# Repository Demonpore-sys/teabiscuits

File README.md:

# teabiscuits

All boards are currently initial revision, have not been brought-up/tested. LMP7721 designs have undergone some breadboarding.

teabiscuits_adc: MAX11169 Based ADC board, single ADC. Based on array board bringup, should work.

teabiscuits_adc_array: MAX11169 Based ADC board, array of 8 ADCs. Quick hack based on teabiscuits_adc. Works, requires hacks on power lines (overlaps with fill).

teabiscuits_adc_4ch: ADAR7521 Based 4 channel ADC board. Regulator comes up with reset, SPI not yet tested.

teabiscuits_amp: LMP7721 Based transimpedance amplifier, uses guarding circuit. Bring up started, see notes on notion.

teabiscuits_amp_mini: LMP7721 Based amplifier, attempt to make a very small board, no guarding. Tested, works.

teabiscuits_amp_mini_bias: LMP7721 Based board with bias control, has been built. r3 will require modifications (see notion)

teabiscuits_dac: AD5791 Based DAC/Bias board.

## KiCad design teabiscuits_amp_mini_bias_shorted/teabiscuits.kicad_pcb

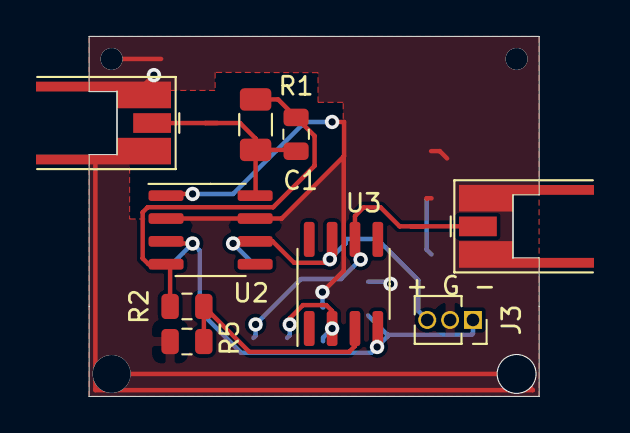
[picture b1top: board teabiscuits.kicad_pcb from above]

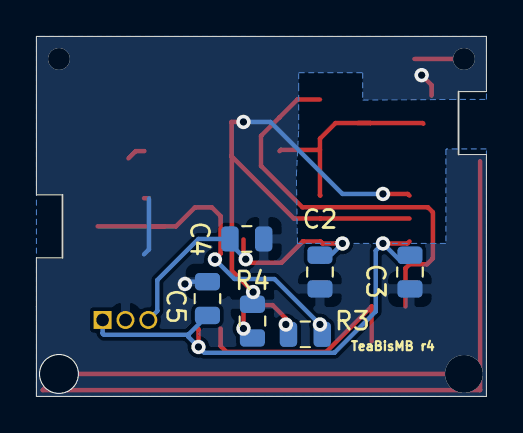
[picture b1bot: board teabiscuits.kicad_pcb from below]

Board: 2 copper layers, 24.9 x 20.0 mm, 15 parts (6 on the bottom side), 8 nets.

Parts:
C1: 2pF; C_0805_2012Metric
C2, C3: 100nF; C_0805_2012Metric
C4, C5: 10nF; C_0805_2012Metric
J1, J2: Conn_Coaxial; MMCX_Molex_73415-0961_Horizontal_1.0mm-PCB
J3: Conn_01x03_Male; PinSocket_1x03_P1.27mm_Vertical
R1: 1M; R_1206_3216Metric
R2, R4: 100; R_0805_2012Metric
R3, R5: 1K; R_0805_2012Metric
U2: LMP7721; SOIC-8_3.9x4.9mm_P1.27mm
U3: OP07; SOIC-8_3.9x4.9mm_P1.27mm

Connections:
+5V: C2.1, C4.1, J3.3, U2.6, U3.7
-5V: C3.1, C5.1, J3.1, U2.3, U3.4
GUARD: C2.2, C3.2, C4.2, C5.2, J1.2, J2.2, J3.2, R4.1, R5.2, U2.1, U2.2, U2.7
unnamed: C1.1, R1.1, R2.2, U2.4
unnamed: C1.2, J1.1, R1.2, U2.8
unnamed: J2.1, R3.1, U3.6
unnamed: R2.1, R5.1, U3.3
unnamed: R3.2, R4.2, U3.2

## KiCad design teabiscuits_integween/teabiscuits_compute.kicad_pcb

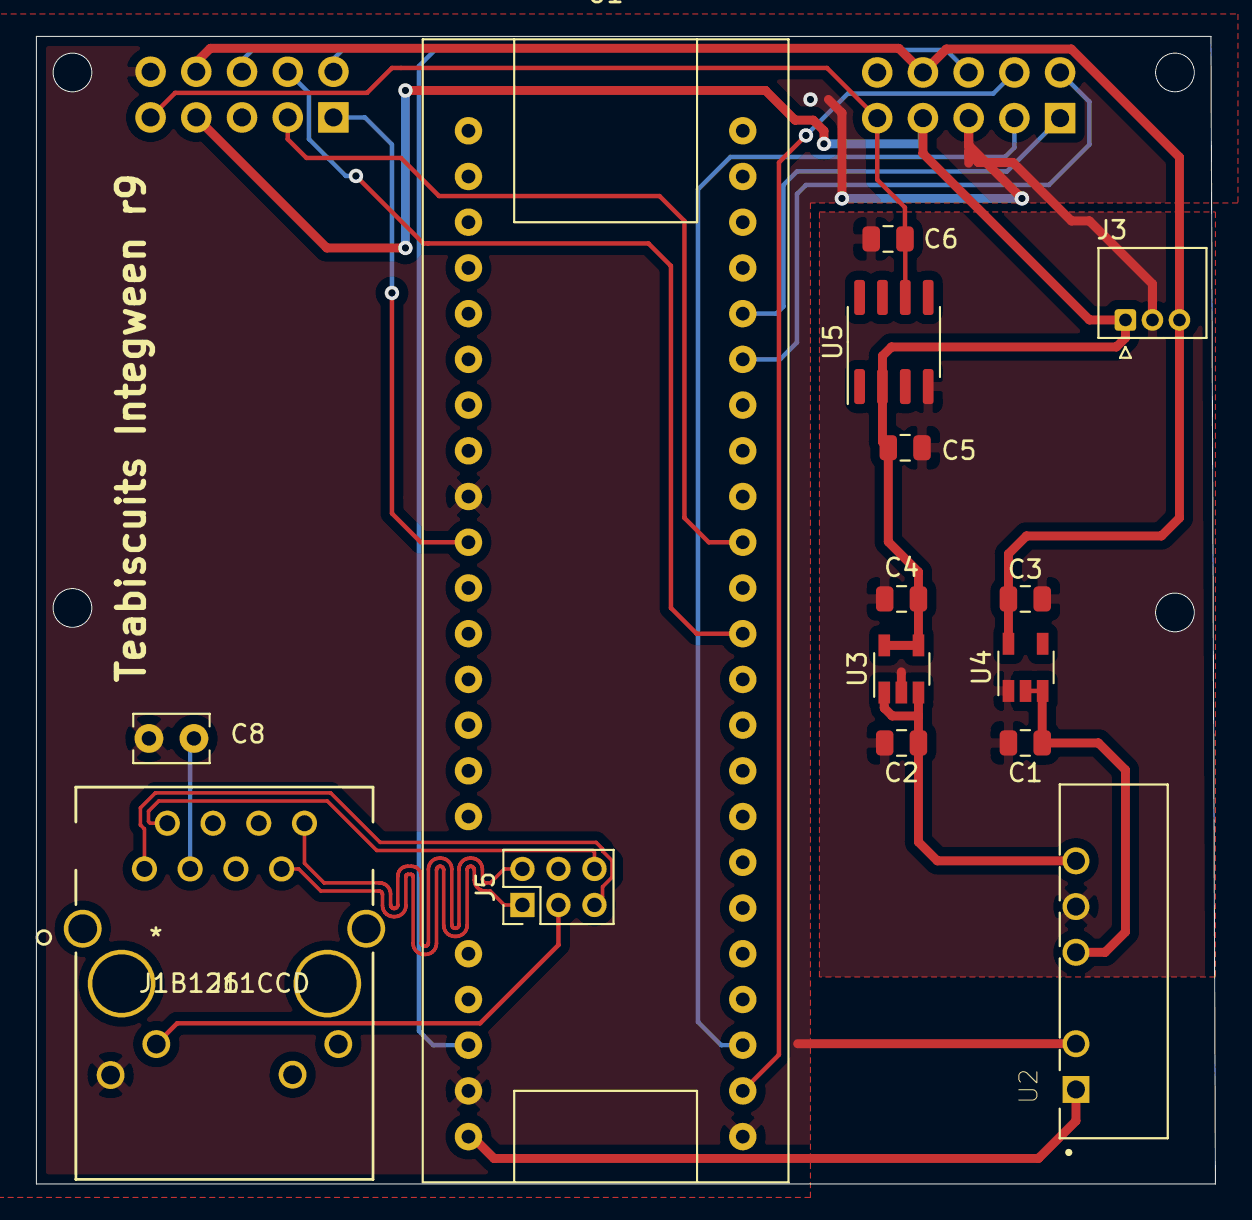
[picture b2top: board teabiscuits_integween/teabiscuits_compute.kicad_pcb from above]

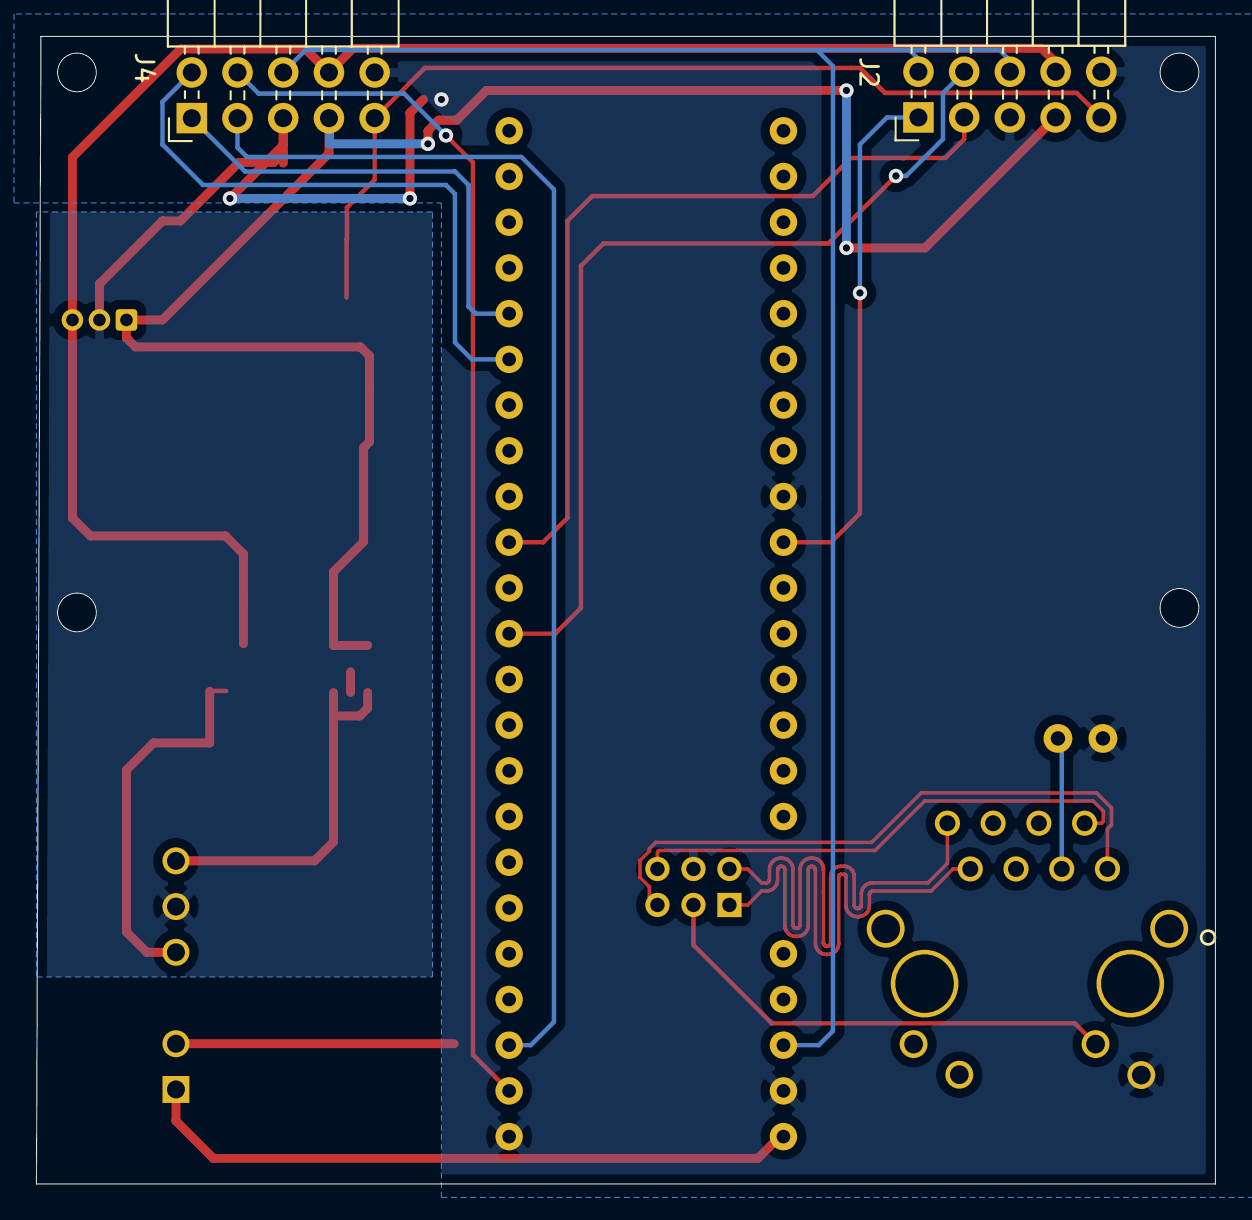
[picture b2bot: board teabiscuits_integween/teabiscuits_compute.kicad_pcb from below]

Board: 2 copper layers, 65.5 x 63.8 mm, 17 parts (2 on the bottom side), 21 nets.

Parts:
C1, C2, C3, C4: 2.2uF; C_0805_2012Metric
C5, C6: 0.1uF; C_0805_2012Metric
C8: CP; C_Rect_L4.0mm_W2.5mm_P2.50mm
J2, J4: Conn_02x05_Odd_Even; PinHeader_2x05_P2.54mm_Horizontal
J3: Conn_01x03; JST
J5: Conn_02x03_Odd_Even; PinHeader_2x03_P2.00mm_Vertical
J6: J1B1211CCD
U1: teensy41
U2: PDME1-S5-D3-S; CONV_PDME1-S5-D3-S
U3: ADP7142AUJZ-2.5; TSOT-23-5
U4: ADP7182AUJZ-2.5; TSOT-23-5
U5: REF5020AD; SOIC-8_3.9x4.9mm_P1.27mm

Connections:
+2V5: C4.1, C5.1, J2.7, J3.1, J4.7, U3.4, U3.5, U5.2
+5V: U1.M6, U2.1
-2V5: C3.1, J2.8, J3.3, J4.8, U4.5
DAC_LDAC: J4.4, U1.0
GND: C1.2, C2.2, C3.2, C4.2, C5.2, C6.2, C8.1, J2.5, J2.10, J3.2, J4.5, J4.10, J5.4, J6.9, U1.M1, U1.M3, U1.M5, U2.2, U2.5, U3.2, U4.1, U5.4
IOREF: J2.2, J2.6, J4.6, U1.M4
LED: J5.3, J6.10
unnamed: C1.1, U2.4, U4.2, U4.3
unnamed: C2.1, U2.6, U3.1, U3.3
unnamed: C8.2, J6.3
R+: J5.1, J6.7
R-: J5.2, J6.8
REF: C6.1, J2.9, J4.9, U5.6
SPI1_MISO: J4.3, U1.1
SPI1_MOSI: J4.2, U1.26
SPI1_SCLK: J4.1, U1.27
SPI4_CS0: J2.4, U1.10
SPI4_MISO: J2.3, U1.12
SPI4_SCLK: J2.1, U1.13
T+: J5.6, J6.2
T-: J5.5, J6.1

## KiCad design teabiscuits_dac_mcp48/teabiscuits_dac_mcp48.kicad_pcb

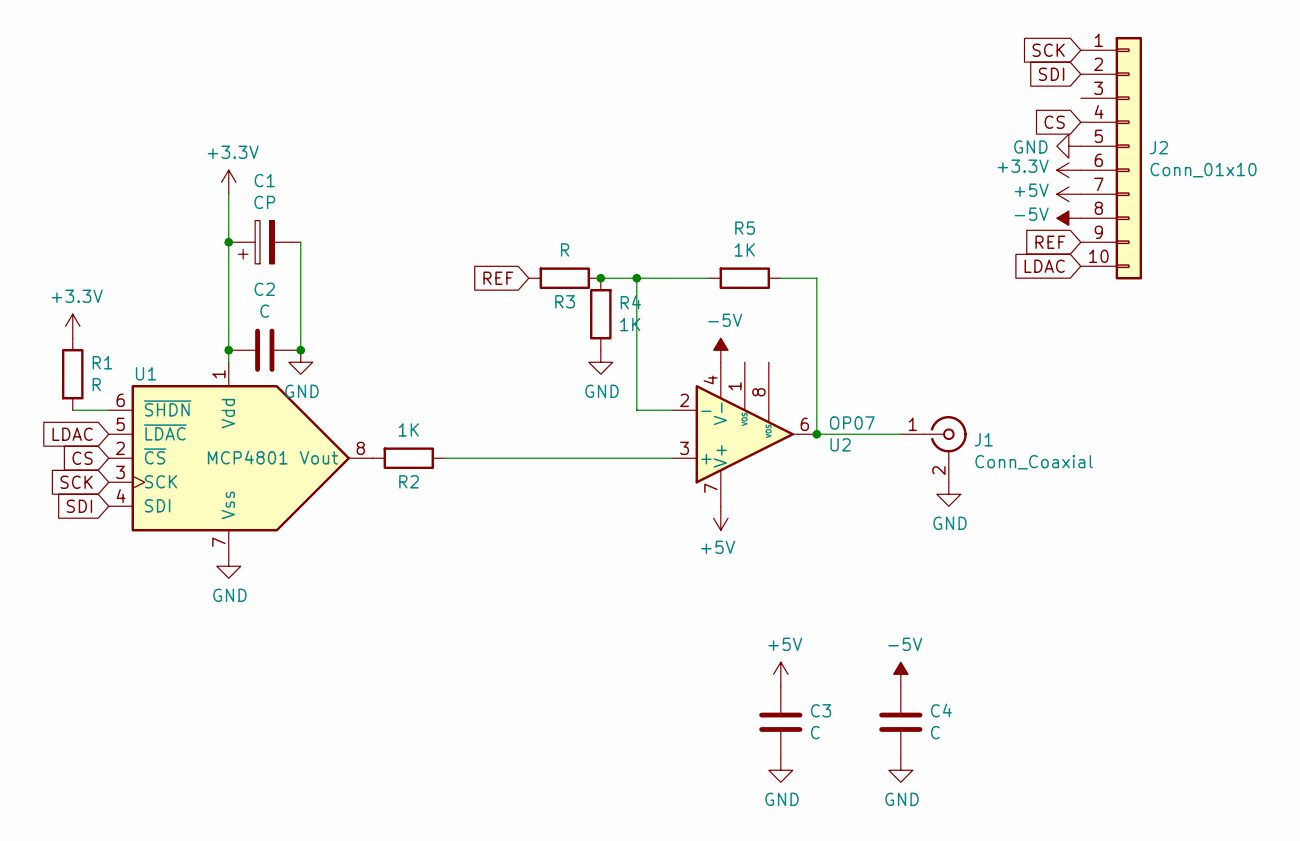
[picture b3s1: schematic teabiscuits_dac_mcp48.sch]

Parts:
C1: CP; CP_EIA-3216-18_Kemet-A
C2, C3, C4: C; C_1206_3216Metric
J1: Conn_Coaxial; MMCX_Molex_73415-0961_Horizontal_1.0mm-PCB
J2: Conn_01x10; PinHeader_2x05_P2.54mm_Horizontal
R1, R3: R; R_1206_3216Metric
R2, R4, R5: 1K; R_1206_3216Metric
U1: MCP4801; SOIC-8_3.9x4.9mm_P1.27mm
U2: OP07; SOIC-8_3.9x4.9mm_P1.27mm

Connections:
+3V3: C1.1, C2.2, J2.6, R1.1, U1.1 (Vdd)
+5V: C3.2, J2.7, U2.7 (V+)
-5V: C4.2, J2.8, U2.4 (V-)
CS: J2.4, U1.2 (~CS)
GND: C1.2, C2.1, C3.1, C4.1, J1.2 (Ext), J2.5, R4.1, U1.7 (Vss)
LDAC: J2.10, U1.5 (~LDAC)
unnamed: J1.1 (In), R5.1, U2.6
unnamed: R1.2, U1.6 (~SHDN)
unnamed: R2.1, U2.3 (+)
unnamed: R2.2, U1.8 (Vout)
unnamed: R3.1, R4.2, R5.2, U2.2 (-)
REF: J2.9, R3.2
SCK: J2.1, U1.3 (SCK)
SDI: J2.2, U1.4 (SDI)

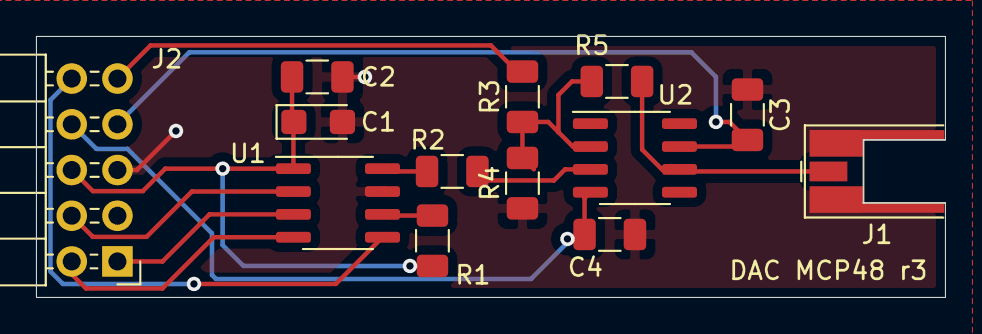
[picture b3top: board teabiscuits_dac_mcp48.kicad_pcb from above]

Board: 2 copper layers, 50.4 x 14.5 mm, 13 parts (0 on the bottom side), 14 nets.

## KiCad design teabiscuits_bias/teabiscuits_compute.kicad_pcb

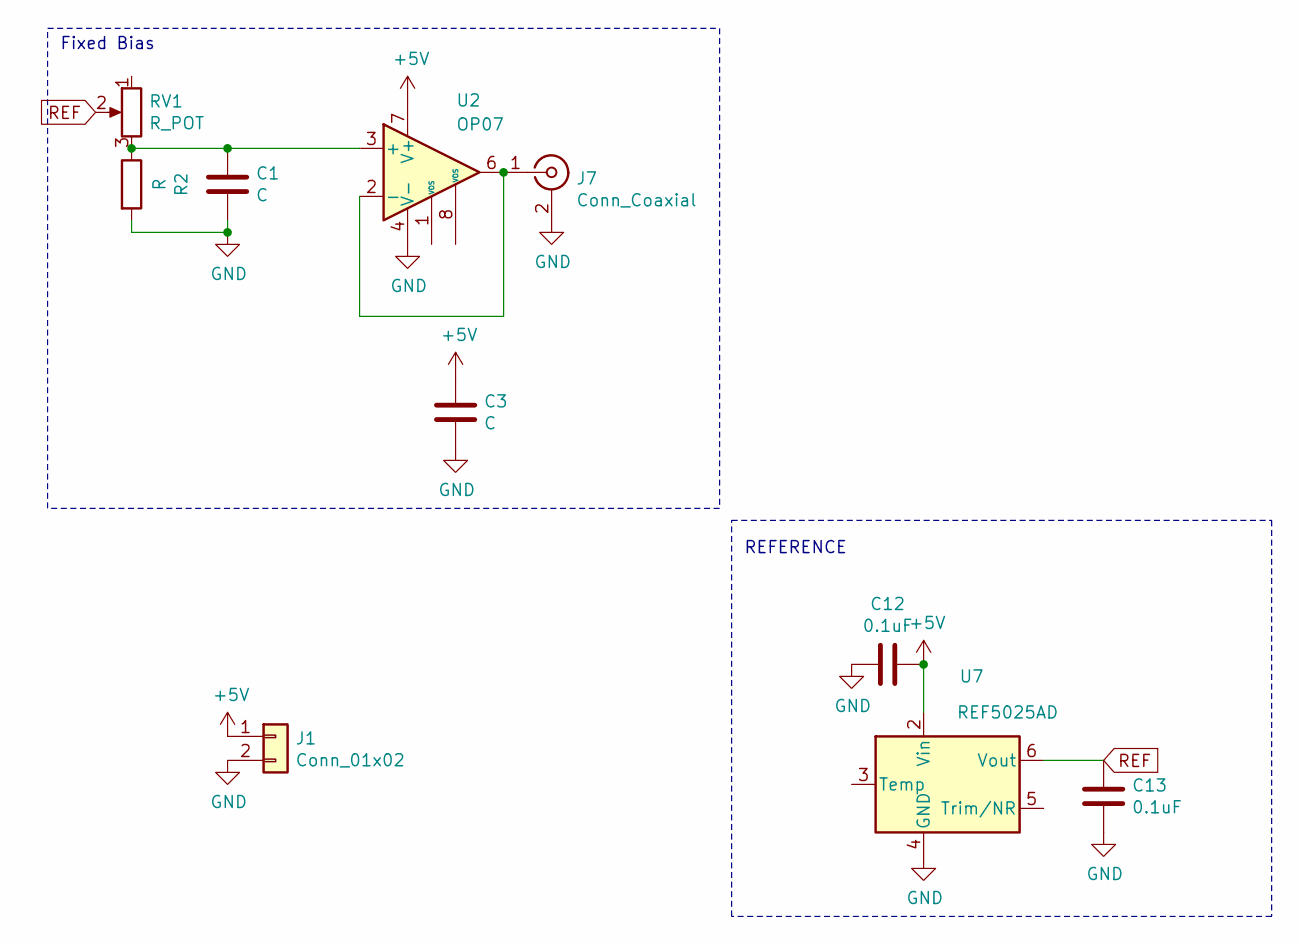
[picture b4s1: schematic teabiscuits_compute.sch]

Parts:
C1, C3: C; C_0805_2012Metric
C12, C13: 0.1uF; C_0805_2012Metric
J1: Conn_01x02; PinHeader_1x02_P2.54mm_Vertical
J7: Conn_Coaxial; MMCX_Molex_73415-0961_Horizontal_1.0mm-PCB
R2: R; R_0805_2012Metric
RV1: R_POT; Potentiometer_WirePads_largePads
U2: OP07; SOIC-8_3.9x4.9mm_P1.27mm
U7: REF5025AD; SOIC-8_3.9x4.9mm_P1.27mm

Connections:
+5V: C3.1, C12.1, J1.1, U2.7 (V+), U7.2 (Vin)
GND: C1.2, C3.2, C12.2, C13.2, J1.2, J7.2 (Ext), R2.2, U2.4 (V-), U7.4 (GND)
unnamed: C1.1, R2.1, RV1.3, U2.3 (+)
unnamed: J7.1 (In), U2.2 (-), U2.6
REF: C13.1, RV1.2, U7.6 (Vout)

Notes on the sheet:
Fixed Bias
REFERENCE

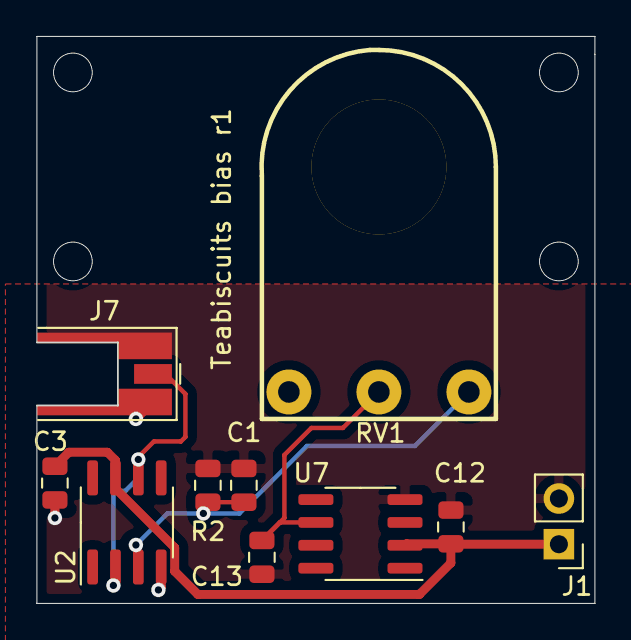
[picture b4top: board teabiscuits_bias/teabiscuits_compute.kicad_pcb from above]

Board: 2 copper layers, 31.0 x 31.4 mm, 10 parts (0 on the bottom side), 5 nets.

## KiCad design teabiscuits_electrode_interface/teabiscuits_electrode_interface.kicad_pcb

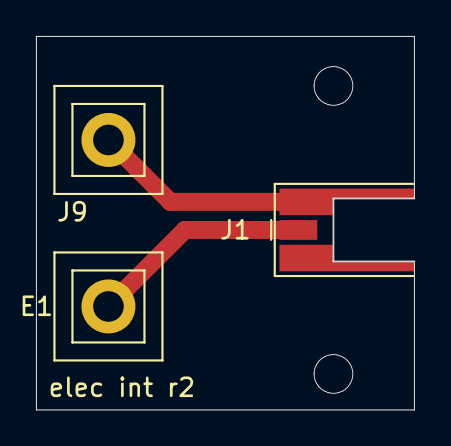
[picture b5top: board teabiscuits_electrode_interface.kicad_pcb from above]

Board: 2 copper layers, 21.0 x 20.7 mm, 3 parts (0 on the bottom side), 2 nets.

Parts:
E1: Conn_01x01; KeystonePost
J1: Conn_Coaxial; MMCX_Molex_73415-0961_Horizontal_1.0mm-PCB
J9: Conn_01x01; KeystonePost

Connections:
GND: J1.2, J9.1
unnamed: E1.1, J1.1

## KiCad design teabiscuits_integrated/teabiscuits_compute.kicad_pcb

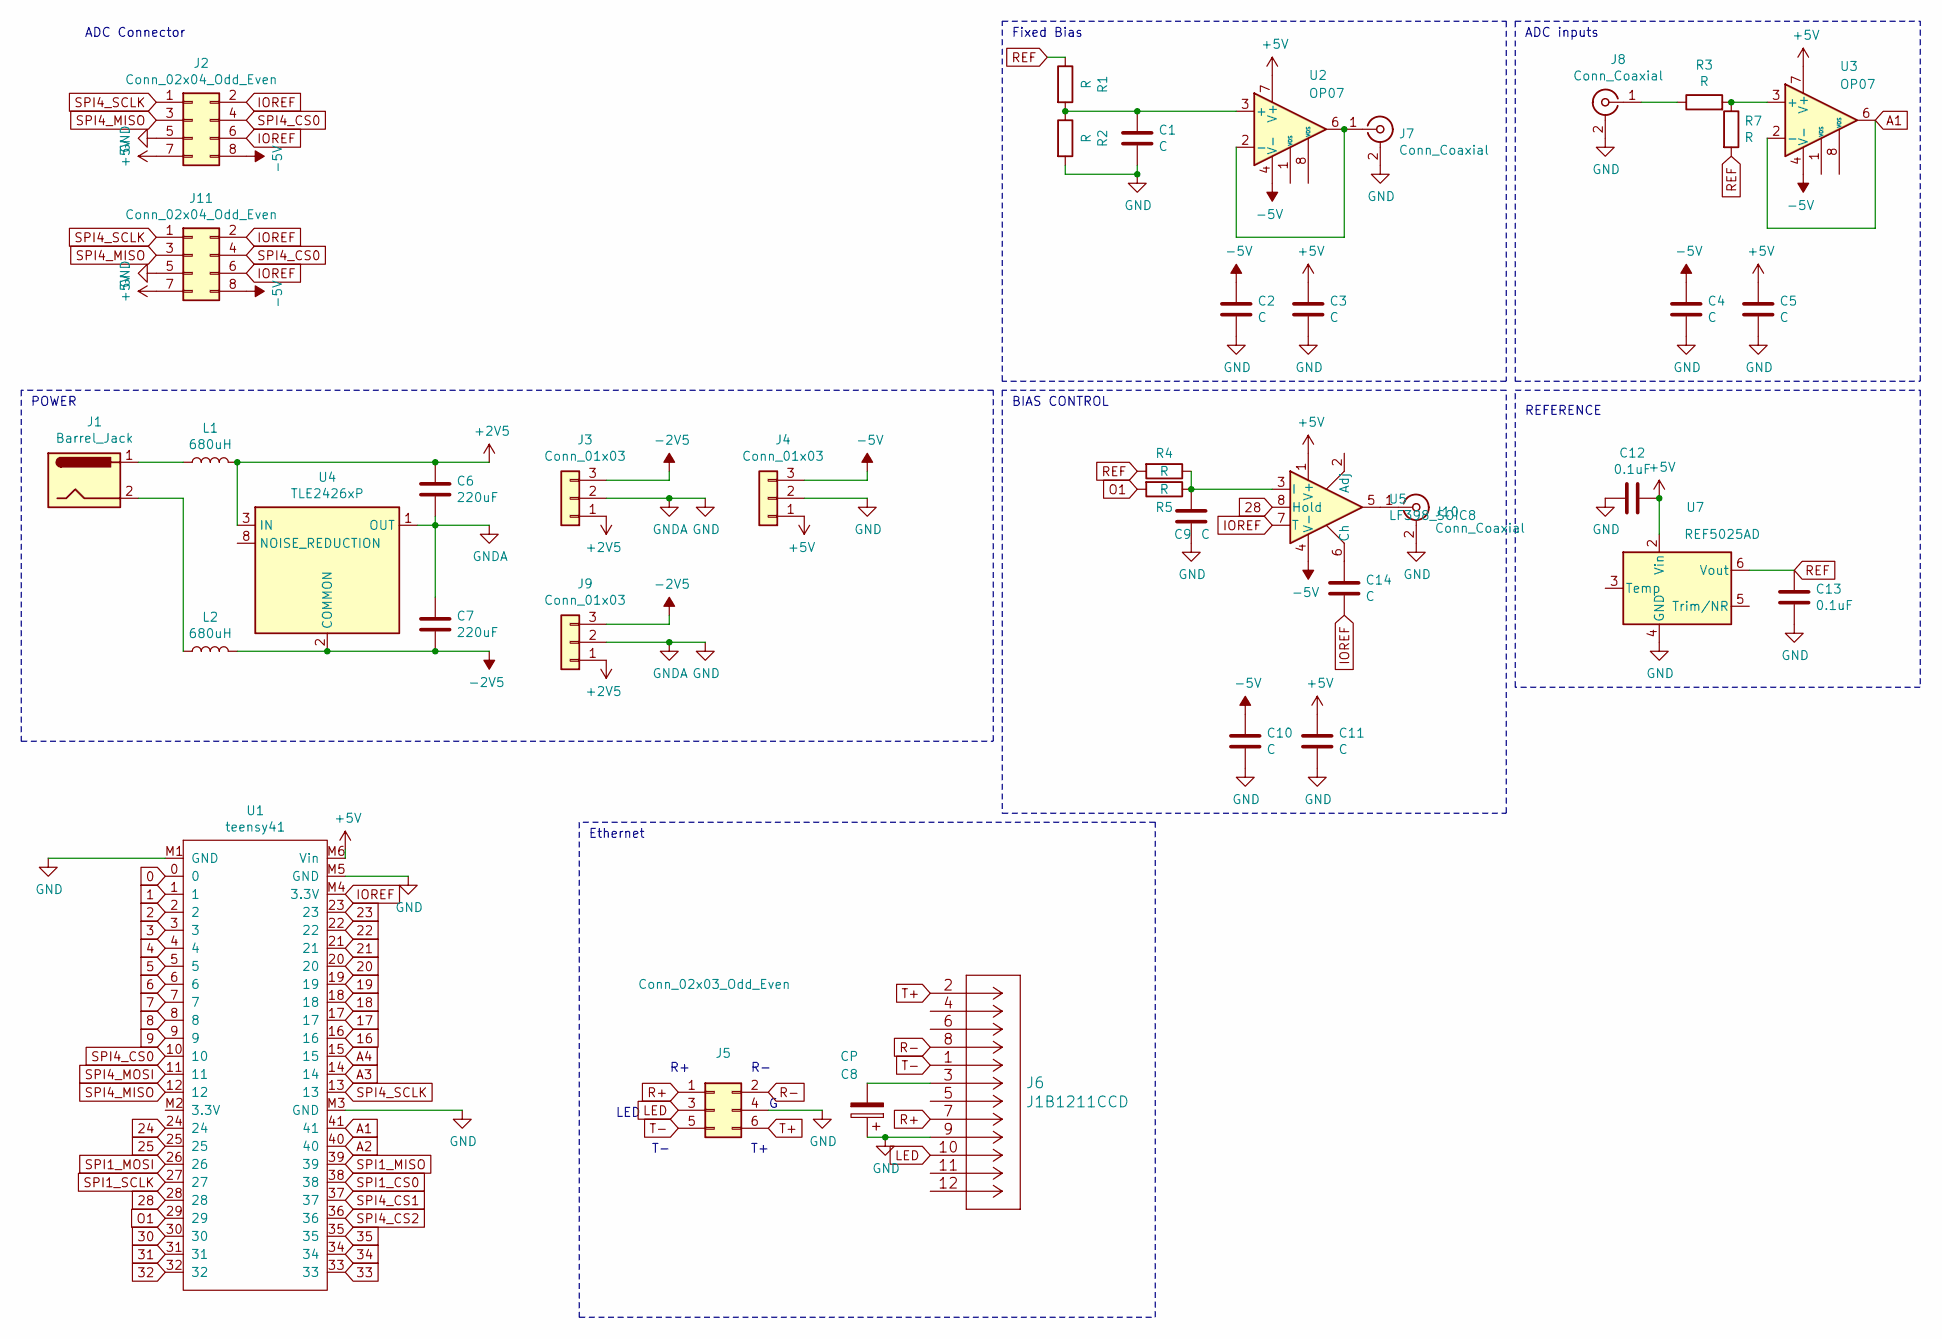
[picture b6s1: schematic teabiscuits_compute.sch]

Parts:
C1, C2, C3, C4, C5, C9, C10, C11, C14: C; C_0805_2012Metric
C6, C7: 220uF; CP_Radial_D5.0mm_P2.00mm
C8: CP; C_Rect_L4.0mm_W2.5mm_P2.50mm
C12, C13: 0.1uF; C_0805_2012Metric
J1: Barrel_Jack; BarrelJack_CUI_PJ-063AH_Horizontal
J2, J11: Conn_02x04_Odd_Even; PinHeader_2x04_P2.54mm_Vertical
J3, J4, J9: Conn_01x03; JST
J5: Conn_02x03_Odd_Even; PinHeader_2x03_P2.00mm_Vertical
J6: J1B1211CCD
J7, J8, J10: Conn_Coaxial; MMCX_Molex_73415-0961_Horizontal_1.0mm-PCB
L1, L2: 680uH; L_Radial_D9.5mm_P5.00mm_Fastron_07HVP
R1, R2, R3, R4, R5, R7: R; R_0805_2012Metric
U1: teensy41
U2, U3: OP07; SOIC-8_3.9x4.9mm_P1.27mm
U4: TLE2426xP; SOIC-8_3.9x4.9mm_P1.27mm
U5: LF398_SOIC8; SOIC-8_3.9x4.9mm_P1.27mm
U7: REF5025AD; SOIC-8_3.9x4.9mm_P1.27mm

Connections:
0: U1.0
1: U1.1
2: U1.2
3: U1.3
4: U1.4
5: U1.5
6: U1.6
7: U1.7
8: U1.8
9: U1.9
16: U1.16
17: U1.17
18: U1.18
19: U1.19
20: U1.20
21: U1.21
22: U1.22
23: U1.23
24: U1.24
25: U1.25
28: U1.28, U5.8 (Hold)
30: U1.30
31: U1.31
32: U1.32
33: U1.33
34: U1.34
35: U1.35
+2V5: C6.1, J3.1, J9.1, L1.2, U4.3 (IN)
+5V: C3.1, C5.1, C11.1, C12.1, J2.7, J4.1, J11.7, U1.M6 (Vin), U2.7 (V+), U3.7 (V+), U5.1 (V+), U7.2 (Vin)
-2V5: C7.2, J3.3, J9.3, L2.2, U4.2 (COMMON)
-5V: C2.1, C4.1, C10.1, J2.8, J4.3, J11.8, U2.4 (V-), U3.4 (V-), U5.4 (V-)
A1: U1.41, U3.2 (-), U3.6
A2: U1.40
A3: U1.14
A4: U1.15
GND: C1.2, C2.2, C3.2, C4.2, C5.2, C6.2, C7.1, C8.1, C9.2, C10.2, C11.2, C12.2, C13.2, J2.5, J3.2, J4.2, J5.4, J6.9, J7.2 (Ext), J8.2 (Ext), J9.2, J10.2 (Ext), J11.5, R2.2, U1.M1 (GND), U1.M3 (GND), U1.M5 (GND), U4.1 (OUT), U7.4 (GND)
IOREF: C14.2, J2.2, J2.6, J11.2, J11.6, U1.M4 (3.3V), U5.7 (T)
LED: J5.3, J6.10
unnamed: C1.1, R1.2, R2.1, U2.3 (+)
unnamed: C8.2, J6.3
unnamed: C9.1, R4.1, R5.1, U5.3 (I)
unnamed: C14.1, U5.6 (Ch)
unnamed: J1.1, L1.1
unnamed: J1.2, L2.1
unnamed: J7.1 (In), U2.2 (-), U2.6
unnamed: J8.1 (In), R3.1
unnamed: J10.1 (In), U5.5
unnamed: R3.2, R7.1, U3.3 (+)
O1: R5.2, U1.29
R+: J5.1, J6.7
R-: J5.2, J6.8
REF: C13.1, R1.1, R4.2, R7.2, U7.6 (Vout)
SPI1_CS0: U1.38
SPI1_MISO: U1.39
SPI1_MOSI: U1.26
SPI1_SCLK: U1.27
SPI4_CS0: J2.4, J11.4, U1.10
SPI4_CS1: U1.37
SPI4_CS2: U1.36
SPI4_MISO: J2.3, J11.3, U1.12
SPI4_MOSI: U1.11
SPI4_SCLK: J2.1, J11.1, U1.13
T+: J5.6, J6.2
T-: J5.5, J6.1

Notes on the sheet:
ADC inputs
Fixed Bias
ADC Connector
REFERENCE
BIAS CONTROL
POWER
Ethernet
LED

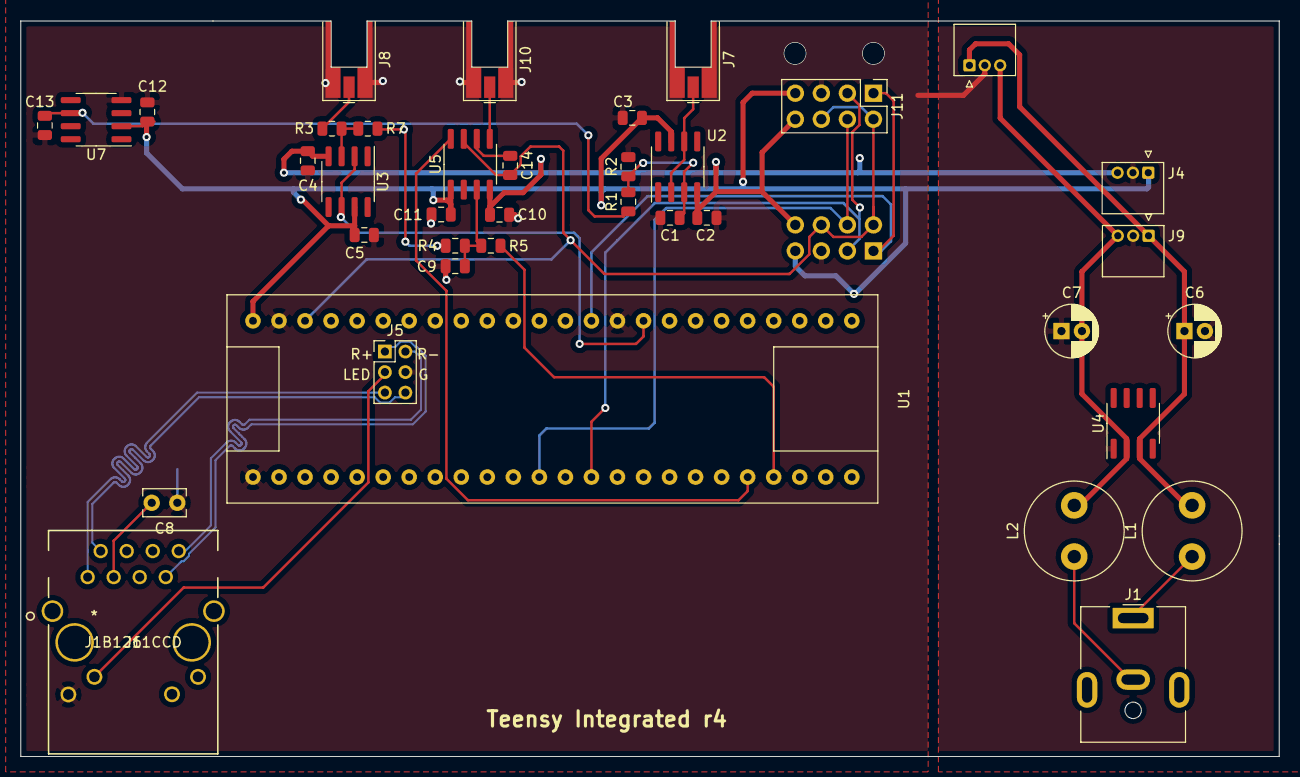
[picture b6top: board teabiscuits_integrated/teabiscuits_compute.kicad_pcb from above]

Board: 2 copper layers, 122.7 x 71.7 mm, 39 parts (1 on the bottom side), 28 nets.

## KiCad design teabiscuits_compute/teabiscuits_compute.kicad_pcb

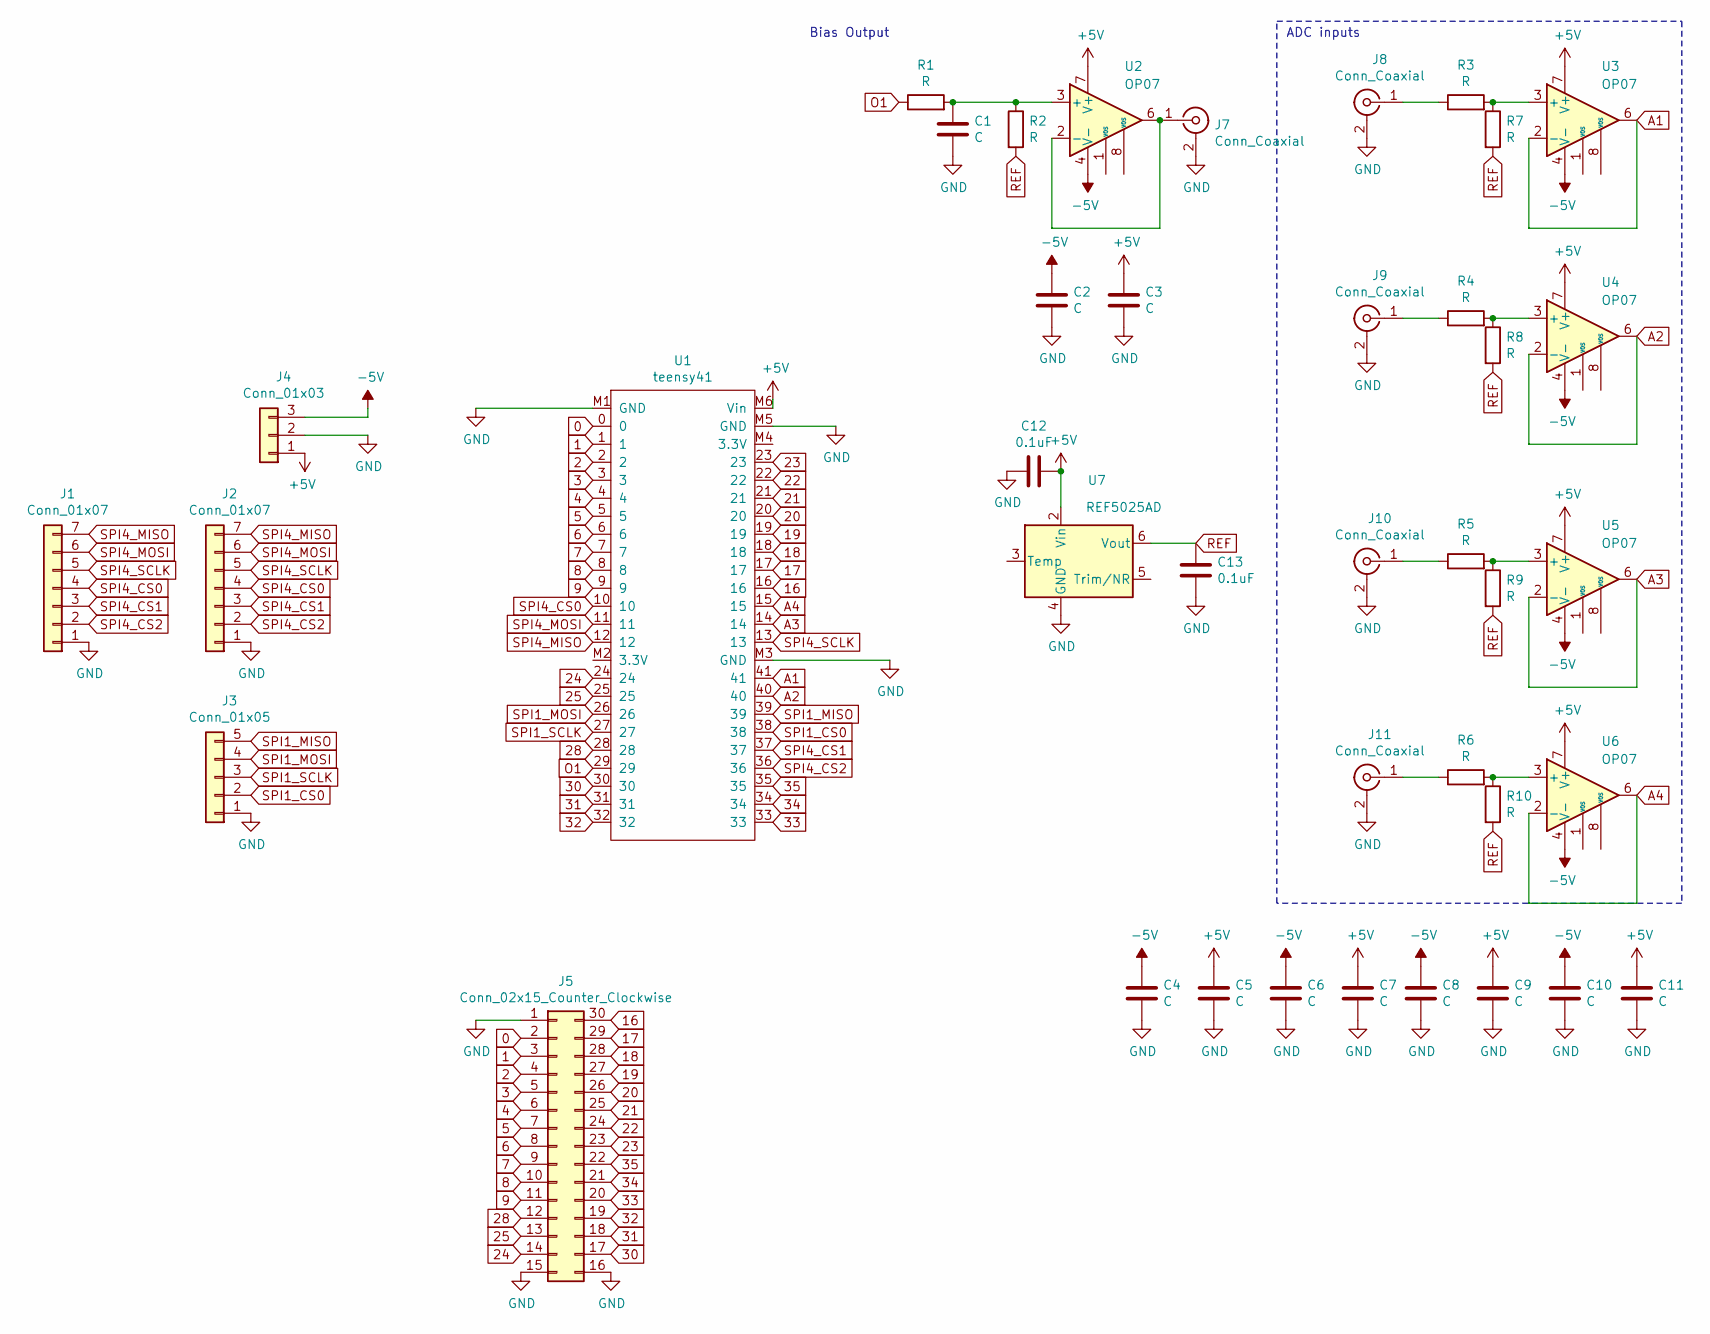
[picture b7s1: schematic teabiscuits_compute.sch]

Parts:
C1, C2, C3, C4, C5, C6, C7, C8, C9, C10, C11: C; C_0805_2012Metric
C12, C13: 0.1uF; C_0805_2012Metric
J1, J2: Conn_01x07; PinHeader_1x07_P2.54mm_Vertical
J3: Conn_01x05; PinHeader_1x05_P2.54mm_Vertical
J4: Conn_01x03; JST
J5: Conn_02x15_Counter_Clockwise; PinHeader_2x15_P2.54mm_Vertical
J7, J8, J9, J10, J11: Conn_Coaxial; MMCX_Molex_73415-0961_Horizontal_1.0mm-PCB
R1, R2, R3, R4, R5, R6, R7, R8, R9, R10: R; R_0805_2012Metric
U1: teensy41
U2, U3, U4, U5, U6: OP07; SOIC-8_3.9x4.9mm_P1.27mm
U7: REF5025AD; SOIC-8_3.9x4.9mm_P1.27mm

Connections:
0: J5.2, U1.0
1: J5.3, U1.1
2: J5.4, U1.2
3: J5.5, U1.3
4: J5.6, U1.4
5: J5.7, U1.5
6: J5.8, U1.6
7: J5.9, U1.7
8: J5.10, U1.8
9: J5.11, U1.9
16: J5.30, U1.16
17: J5.29, U1.17
18: J5.28, U1.18
19: J5.27, U1.19
20: J5.26, U1.20
21: J5.25, U1.21
22: J5.24, U1.22
23: J5.23, U1.23
24: J5.14, U1.24
25: J5.13, U1.25
28: J5.12, U1.28
30: J5.17, U1.30
31: J5.18, U1.31
32: J5.19, U1.32
33: J5.20, U1.33
34: J5.21, U1.34
35: J5.22, U1.35
A1: U1.41, U3.2 (-), U3.6
A2: U1.40, U4.2 (-), U4.6
A3: U1.14, U5.2 (-), U5.6
A4: U1.15, U6.2 (-), U6.6
GND: C1.2, C2.2, C3.2, C4.2, C5.2, C6.2, C7.2, C8.2, C9.2, C10.2, C11.2, C12.2, C13.2, J1.1, J2.1, J3.1, J4.2, J5.1, J5.15, J5.16, J7.2 (Ext), J8.2 (Ext), J9.2 (Ext), J10.2 (Ext), J11.2 (Ext), U1.M1 (GND), U1.M3 (GND), U1.M5 (GND), U7.4 (GND)
unnamed: C1.1, R1.2, R2.1, U2.3 (+)
unnamed: J7.1 (In), U2.2 (-), U2.6
unnamed: J8.1 (In), R3.1
unnamed: J9.1 (In), R4.1
unnamed: J10.1 (In), R5.1
unnamed: J11.1 (In), R6.1
unnamed: R3.2, R7.1, U3.3 (+)
unnamed: R4.2, R8.1, U4.3 (+)
unnamed: R5.2, R9.1, U5.3 (+)
unnamed: R6.2, R10.1, U6.3 (+)
O1: R1.1, U1.29
REF: C13.1, R2.2, R7.2, R8.2, R9.2, R10.2, U7.6 (Vout)
SPI1_CS0: J3.2, U1.38
SPI1_MISO: J3.5, U1.39
SPI1_MOSI: J3.4, U1.26
SPI1_SCLK: J3.3, U1.27
SPI4_CS0: J1.4, J2.4, U1.10
SPI4_CS1: J1.3, J2.3, U1.37
SPI4_CS2: J1.2, J2.2, U1.36
SPI4_MISO: J1.7, J2.7, U1.12
SPI4_MOSI: J1.6, J2.6, U1.11
SPI4_SCLK: J1.5, J2.5, U1.13

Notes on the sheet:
ADC inputs
Bias Output

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
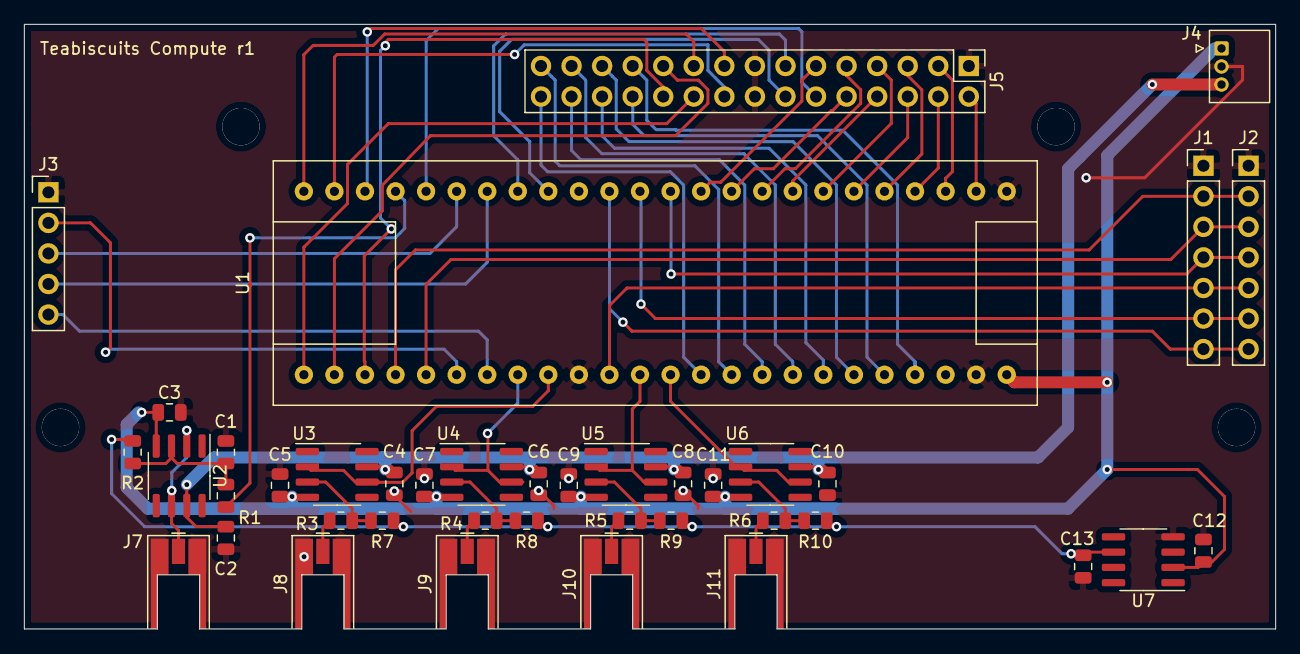
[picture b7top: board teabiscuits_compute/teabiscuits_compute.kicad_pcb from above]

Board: 2 copper layers, 104.0 x 50.2 mm, 40 parts (0 on the bottom side), 56 nets.

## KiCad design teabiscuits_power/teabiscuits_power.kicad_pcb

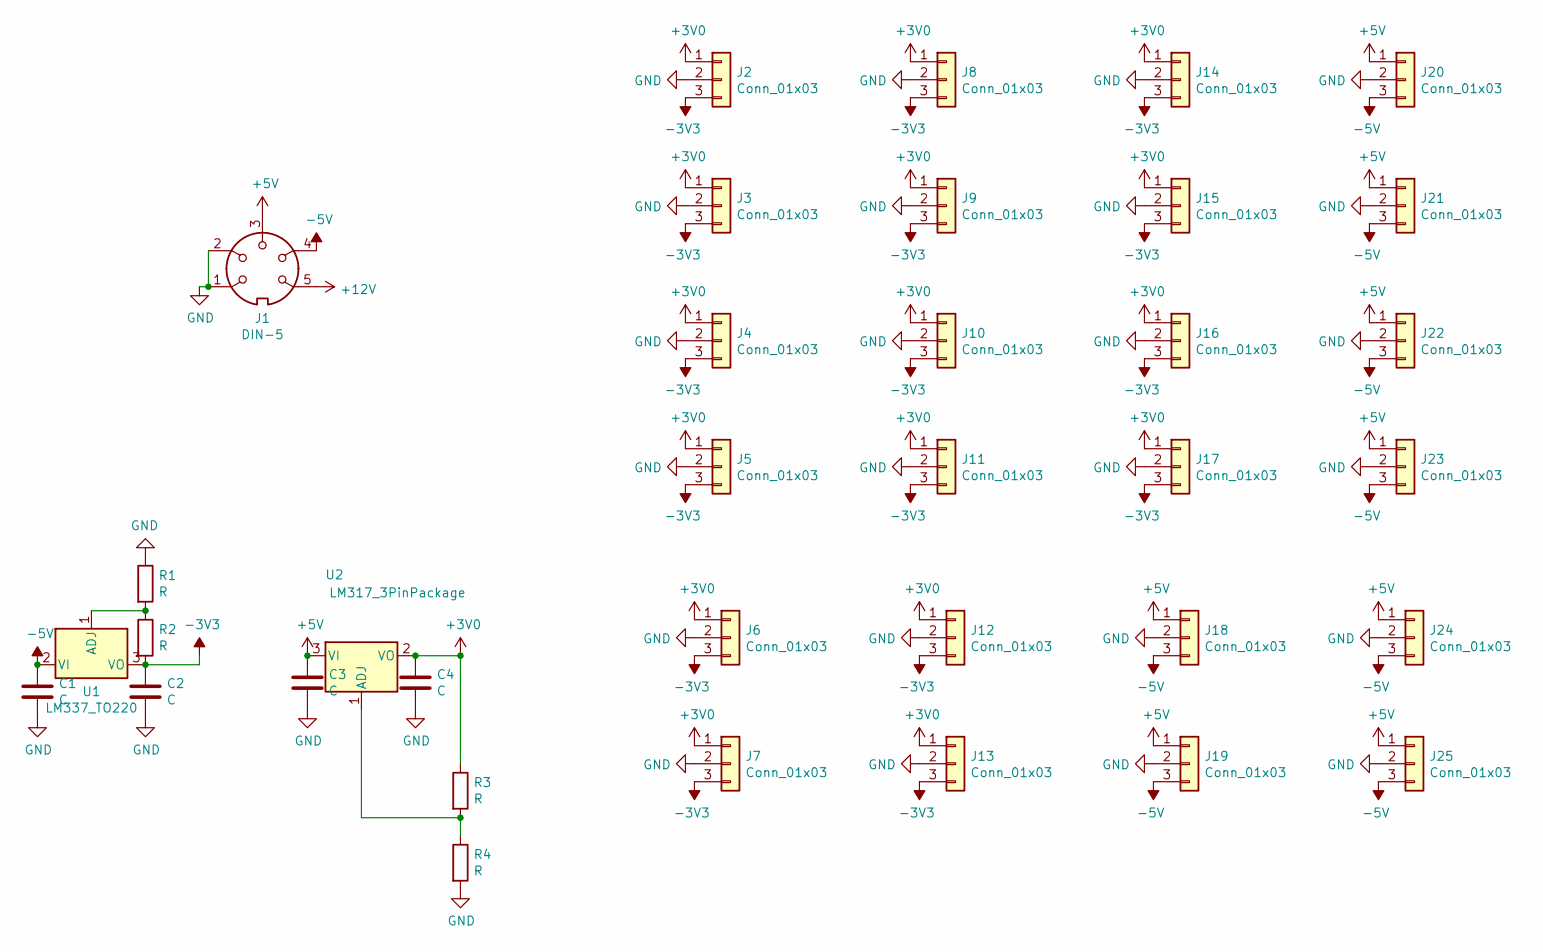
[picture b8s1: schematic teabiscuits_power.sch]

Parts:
C1, C2, C3, C4: C; C_0805_2012Metric
J1: DIN-5; CUI_SDS-50J
J2, J3, J4, J5, J6, J7, J8, J9, J10, J11, J12, J13, J14, J15, J16, J17, J18, J19, J20, J21, J22, J23, J24, J25: Conn_01x03; JST_EH_S3B-EH_1x03_P2.50mm_Horizontal
R1, R2, R3, R4: R; R_0805_2012Metric
U1: LM337_TO220; TO-220-3_Vertical
U2: LM317_3PinPackage; TO-220-3_Vertical

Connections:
+3V0: C4.1, J2.1, J3.1, J4.1, J5.1, J6.1, J7.1, J8.1, J9.1, J10.1, J11.1, J12.1, J13.1, J14.1, J15.1, J16.1, J17.1, R3.1, U2.2 (VO)
+5V: C3.1, J1.3, J18.1, J19.1, J20.1, J21.1, J22.1, J23.1, J24.1, J25.1, U2.3 (VI)
+12V: J1.5
-3V3: C2.1, J2.3, J3.3, J4.3, J5.3, J6.3, J7.3, J8.3, J9.3, J10.3, J11.3, J12.3, J13.3, J14.3, J15.3, J16.3, J17.3, R2.2, U1.3 (VO)
-5V: C1.1, J1.4, J18.3, J19.3, J20.3, J21.3, J22.3, J23.3, J24.3, J25.3, U1.2 (VI)
GND: C1.2, C2.2, C3.2, C4.2, J1.1, J1.2, J2.2, J3.2, J4.2, J5.2, J6.2, J7.2, J8.2, J9.2, J10.2, J11.2, J12.2, J13.2, J14.2, J15.2, J16.2, J17.2, J18.2, J19.2, J20.2, J21.2, J22.2, J23.2, J24.2, J25.2, R1.1, R4.2
unnamed: R1.2, R2.1, U1.1 (ADJ)
unnamed: R3.2, R4.1, U2.1 (ADJ)

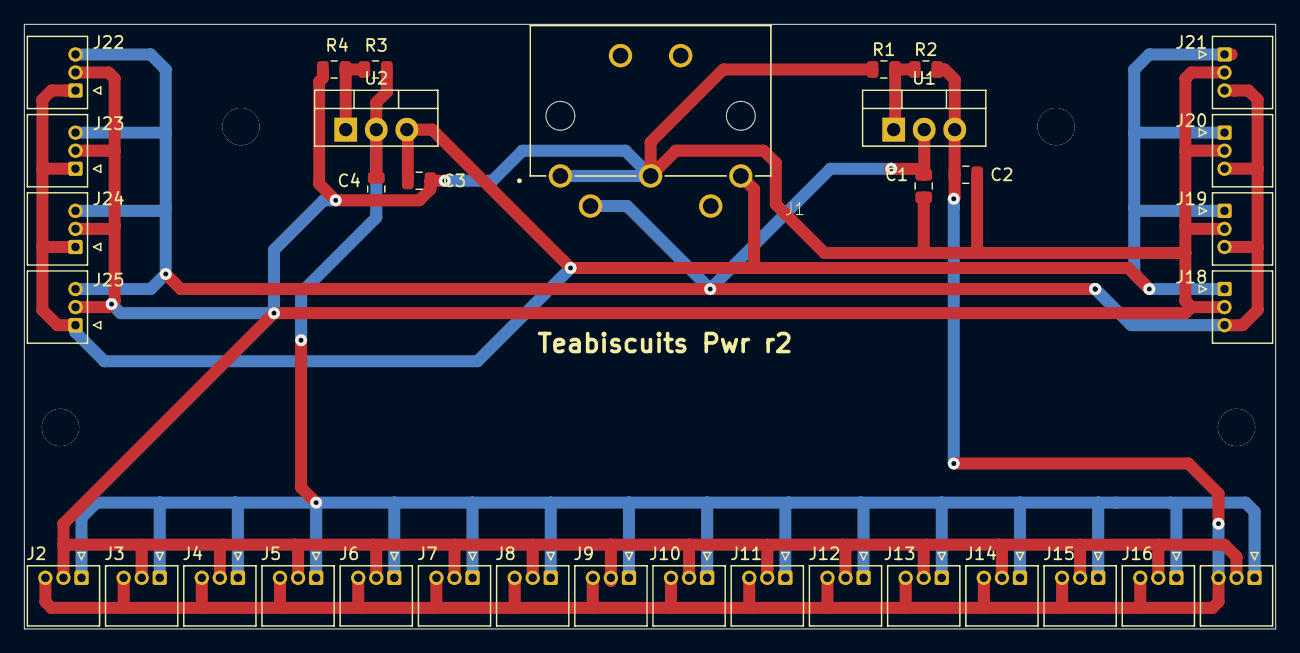
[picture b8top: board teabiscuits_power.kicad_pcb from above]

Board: 2 copper layers, 104.0 x 50.2 mm, 35 parts (0 on the bottom side), 7 nets.

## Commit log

2020-06-25 Initial checkin of Kicad design files
2020-06-25 Updated formating
2020-06-27 4Channel ADC design
2020-06-28 As shipped
2020-06-30 Version of small amplifier with bias input
2020-07-04 Added test code
2020-07-04 updated testcode with config note
2020-07-06 Added test code for daisychain operation
2020-07-06 Fast and slow test code
2020-07-08 Electrode interface design
2020-08-03 Misc updates
2020-08-03 Added power board
2020-08-03 Teensy based compute board
2020-08-03 Amplifier with bias updated to correct for offset
2020-08-03 Revised electrode interface (bigger holes) and power (connector was wrong way round)
2020-08-30 Fixes to compute board
2020-09-02 Integrated compute board
2020-10-02 r4 of integrated pcb
2020-10-13 Electrode interface (single channel version)
2020-10-13 Hacked layout for easier assembly
2020-10-18 missing files
2020-10-23 Added schematic pdf
2020-10-24 Updated DAC layout
2020-11-05 Integween r8
2020-11-05 integween r9
2020-11-05 MCP48 DAC r3
2020-11-13 Current board designs
2020-11-13 Integween prototype
2021-07-09 This is the teabiscuit mini bias amplifier with the bias shorted
    This should have the same size and configuration as the teabiscuit
    mini bias, but without the need for the shorting plug that we've
    been using to short the bias. (The bias has never tested well)
2021-07-09 Some strangeness
    I'm not exactly sure why these are changes, but ... I'm checking them
    in all the same...

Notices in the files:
parts and their libraries:
Copyright 2016 Accelerated Designs. All rights reserved.
